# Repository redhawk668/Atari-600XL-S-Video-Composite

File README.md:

# Atari 600XL S-Video & Composite clean video.

I've designed this, because the 600XL doesn't have an s-video output. S-video output is actually a lot better than composite output. The composite output of the 600XL is quite bad, very blurry. After removing capacitor C109 it gets a lot less blurry, but it still isn't very nice to look at.

This circuit bypasses the 600XL's video circuit to get as clean as possible s-video output. It takes the signals straight from the GTIA, the luma signals are buffered with a 74HC4050 buffer/hex inverter, the buffer/resistor ladder is actually re-used from the original circuit. Chroma is passed through a resistor and a capacitor.
The resulting signals are then passed through a THS7314 filter/amplifier to create the seperate luma/chroma and composite signals.

It also provides composite output, not only s-video output. All signals are provided through the 5 pin DIN connector, they are compatible with existing s-video/composite cables.

It replaces the RF modulator, so that has to be removed. To expose the needed signals from the GTIA, pins 21,22,23,24,25 & 31 have to be lifted out of the socket and wires need to be soldered to those pins. Those will connect to the input pins on the s-video PCB. 

Although, this has been designed with the 600XL in mind, it should also work on the 800XL. The video circuit is basically the same as the 600XL's, only some older 800XL's don't have the chroma line connected. This PCB should solve that problem too.
However, the 800XLF has chroma connected. The XE series also have the chroma line connected. Unfortunatley. this PCB does not fit in the modulator space on an XE.

It provides improved video on NTSC machines as well.

# Rev. A

Top:

Bottom:

Installed in a 600XL:

# Billing of Materials:

|Qty |Value  |Component    |Package          |Parts                    |Description              |
|----|-------|-------------|-----------------|-------------------------|-------------------------|
| 7x | 1K    | Res805      | 0805            | R1,R2,R3,R4,R5,R14,R15  | Resistors               |
| 1x | 36K   | Res805      | 0805            | R6                      | Resistor                |
| 1x | 18K   | Res805      | 0805            | R7                      | Resistor                |
| 1x | 9K1   | Res805      | 0805            | R8                      | Resistor                |
| 1x | 4K7   | Res805      | 0805            | R9                      | Resistor                |
| 1x | 750R  | Res805      | 0805            | R10                     | Resistor                |
| 1x | 1K6   | Res805      | 0805            | R11                     | Resistor                |
| 1x | 2K    | Res805      | 0805            | R12                     | Resistor                |
| 1x | 18K   | Res805      | 0805            | R13                     | Resistor                |
| 3x | 75R   | Res805      | 0805            | R16,R17,R21             | Resistor                |
| 1x | 2K2   | Res805      | 0805            | R19                     | Resistor                |
| 2x | 3K3   | Res805      | 0805            | R20,R22                 | Resistor                |
| 1x | 22uF  | CP_Elec     | Can 6.3x5.3     | C1                      | Electrolytic Capacitor  |
| 5x | 0.1uF | Cap0805     | 0805            | C2,C3,C4,C5,C6          | Ceramic Capacitor       |
| 1x | 1N4148| DIODE323    | SOD-323         | CR1                     | 1N4148 Diode            |
| 1x | BC847 | Trans323    | SOT-323/SC70    | Q1                      | BC847 Transistor        |
| 1x | 4050  | HEXBuffer   | SOP-16          | U1                      | 74HC4050 Buffer         |
| 1x | 7314  | VideoFilter | SOIC-8          | U2                      | THS7314 Video/Filter    |
| 1x |       | Header      | 6x PinHeader    | GTIA Input              | 6x Angled PinHeader     |
| 1x |       | Header      | 3x PinHeader    | Output                  | 3x Straight PinHeader   |
| 1x |       | Header      | 2x PinHeader    | PCB mount               | 2x Straight PinHeader   |
| 1x |       | Header      | 3x PinHeader    | PCB Mount               | 3x Straight PinHeader   |

# Additional steps for installation in an NTSC 600XL

Installing the circuit in an NTSC 600XL is only marginally more difficult than the PAL version; three additional steps are required:

1. Desolder and remove the channel select switch
2. Install a 5-pin DIN PCB mount socket
3. Cut a suitable hole in the case for the DIN connector

Additional parts:

|Qty |Value  |Component    |Package          |Parts                    |Description              |
|----|-------|-------------|-----------------|-------------------------|-------------------------|
| 1x |       | Socket      | 5-pin DIN       | PCB Mount               | Standard DIN connector  |

You also need to make/purchase a 5-pin DIN composite/s-video/audio cable; the same one the Atari 800 uses (there are several good sources for pre-made cables)

# Detailed installation guide (PAL and NTSC 600XL)

This guide will point out differences between PAL and NTSC installation steps, where relevant.

Before you begin:

This project requires surface-mount soldering skills; most parts are fairly easy to work with - the diode and transistor are the smallest parts (SOD-323), with the diode pads being very small. Be sure you can solder SMD, or know someone who can.

The pre-generated Gerber files included in the repository should be directly 'uploadable' to most PCB manufacturers without modification. It is a 4-layer board - nothing out of the ordinary to note. The cost to manufacturer 5 boards is likely less than $20.

The parts list is accurate; most parts should be available and in stock from major electronic part suppliers.

Once you receive your PCB and parts, solder the parts to the board using your preferred method (solder, flux, wave, etc.) and check for any shorts or cold solder joints; the circuit is fairly small and should only take a few minutes to verify against the schematic. Your finished PCB should look similar to the following images. Note that the downward-facing PC pins are designed to fit into ground plane holes that used to hold the RF modulator.

Top View

Bottom View

Follow an online guide to open the 600XL, disconnect the keyboard, remove the main PCB and remove RF shielding, leaving just the main PCB. There are many excellent online guides available.

NTSC models: You'll need to desolder and remove the channel switch and identify the DIN jack placement.

Switch removal and DIN jack pads for NTSC

On the bottom of the PCB, the Chroma connector is tied to ground, which has to be broken for the modification to work. The trace on the PCB is fairly thick, but will still roll-up once you cut your way though with a sharp knife.

Bridge to Remove (PAL and NTSC)

For PAL and NTSC versions, the RF modulator needs to be removed. There are 8 points to desolder; the four wires are easy, the four RF case grounding pads are somewhat more stubborn.

RF Modulator Desolder Points

Once the modulator is removed, the next step is to solder the board into place. The ground pins on the board should fit into the RF case ground points (ensure as much solder as possible is removed from the holes to facilitate installation). The board should not make contact with the ground plane, but "float" a mm or two above the board surface. Position and solder the board, making sure it is square and not overhanging the back of the main PCB.

5-pin DIN Installation (NTSC)

Use a desoldering tool to remove residual solder from the DIN mounting holes, making sure the DIN socket dry-fits, including the front two stabilizing pins, which were previously hidden by the switch. Install and solder the DIN socket into place.

Installed Board and DIN socket

Lift GTIA Pins

6 pins on the GTIA chip need to be lifted outside the socket to disconnect them from the existing circuit and enable connection to the board. As mentioned above, the pins are: 21,22,23,24,25 & 31

GTIA Pins to be Lifted

Solder PC pin connectors, or straight wire onto the lifted pins to the corresponding pins on the board, being careful to avoid any shorts.

Power

Solder a PC pin connector or wire from the +5V pin to the third RF wire solder pad from the left.

Power Connector

Soldered to GTIA and Power

Connect output pins to DIN socket

The board generates Luma, Comp. and Chroma signals - all of which need to be connected to the DIN connector. For NTSC and PAL, the audio and ground pins are already connected on the board and no modification is necessary to these pins. 

5-pin DIN Connector

The Luma pad on PAL and NTSC boards is unpopulated - solder a PC pin connector or wire from the board Luma pin to the first DIN jack position. 

The Comp. pad on PAL is connected to a [formerly] active circuit - lift the leg of R137 closest to the DIN connector and solder the end of a PC pin connector or wire to the now vacant pad and connect to the Comp. output on the board. For NTSC, the R137 pad connected to pin 2 of the DIN connector should be unpopulated - solder the end of a PC pin connector to this pad and connect to the Comp. board output.

The DIN Chroma connector (pin 4) is unpopulated on PAL and NTSC boards, and should have been disconnected from ground by lifting the trace (as above). Solder a PC pin connector to the pad of DIN pin 4 and connect to the Chroma output of the board.

Output Connectors Soldered

If your PC pin connectors are tall, the output pins may need to be bent towards the DIN connector to allow the connectors to clear the RF shielding. Use pliers to bend the pins to a 45 degree angle and slightly towards the front of the PCB.

For NTSC boards, use a Dremel or equivalent tool to cut out a suitable hole for the DIN connector in the case. The hole is roughly centered horizontally on either side of the switch slot, and at the same height (and size) as the power DIN connector. You can use the power DIN connector as a template.

On PAL and NTSC boards, there will be a hole where the RF modulator used to be, which can be filled or capped. 

Follow an online guide to reassamble the 600XL and connect the DIN video connector to s-video and audio. Turn the power on and ensure your monitor is set to s-video. You should see a picture, but the tint will likely be off. Use the tint adjustment on your monitor to adjust the tint until it looks correct. At the same time, adjust brightness and contrast to appropriate levels. The picture should be very clear with practically no interference. If your monitor does not have s-video, the board also outputs composite video, which is very clear as well. Connect composite and audio connectors from the DIN cable to your monitor and adjust. Examples of s-video picture quality from an LCD monitor below.

Close up of READY

Track and Field Title

Track and Field

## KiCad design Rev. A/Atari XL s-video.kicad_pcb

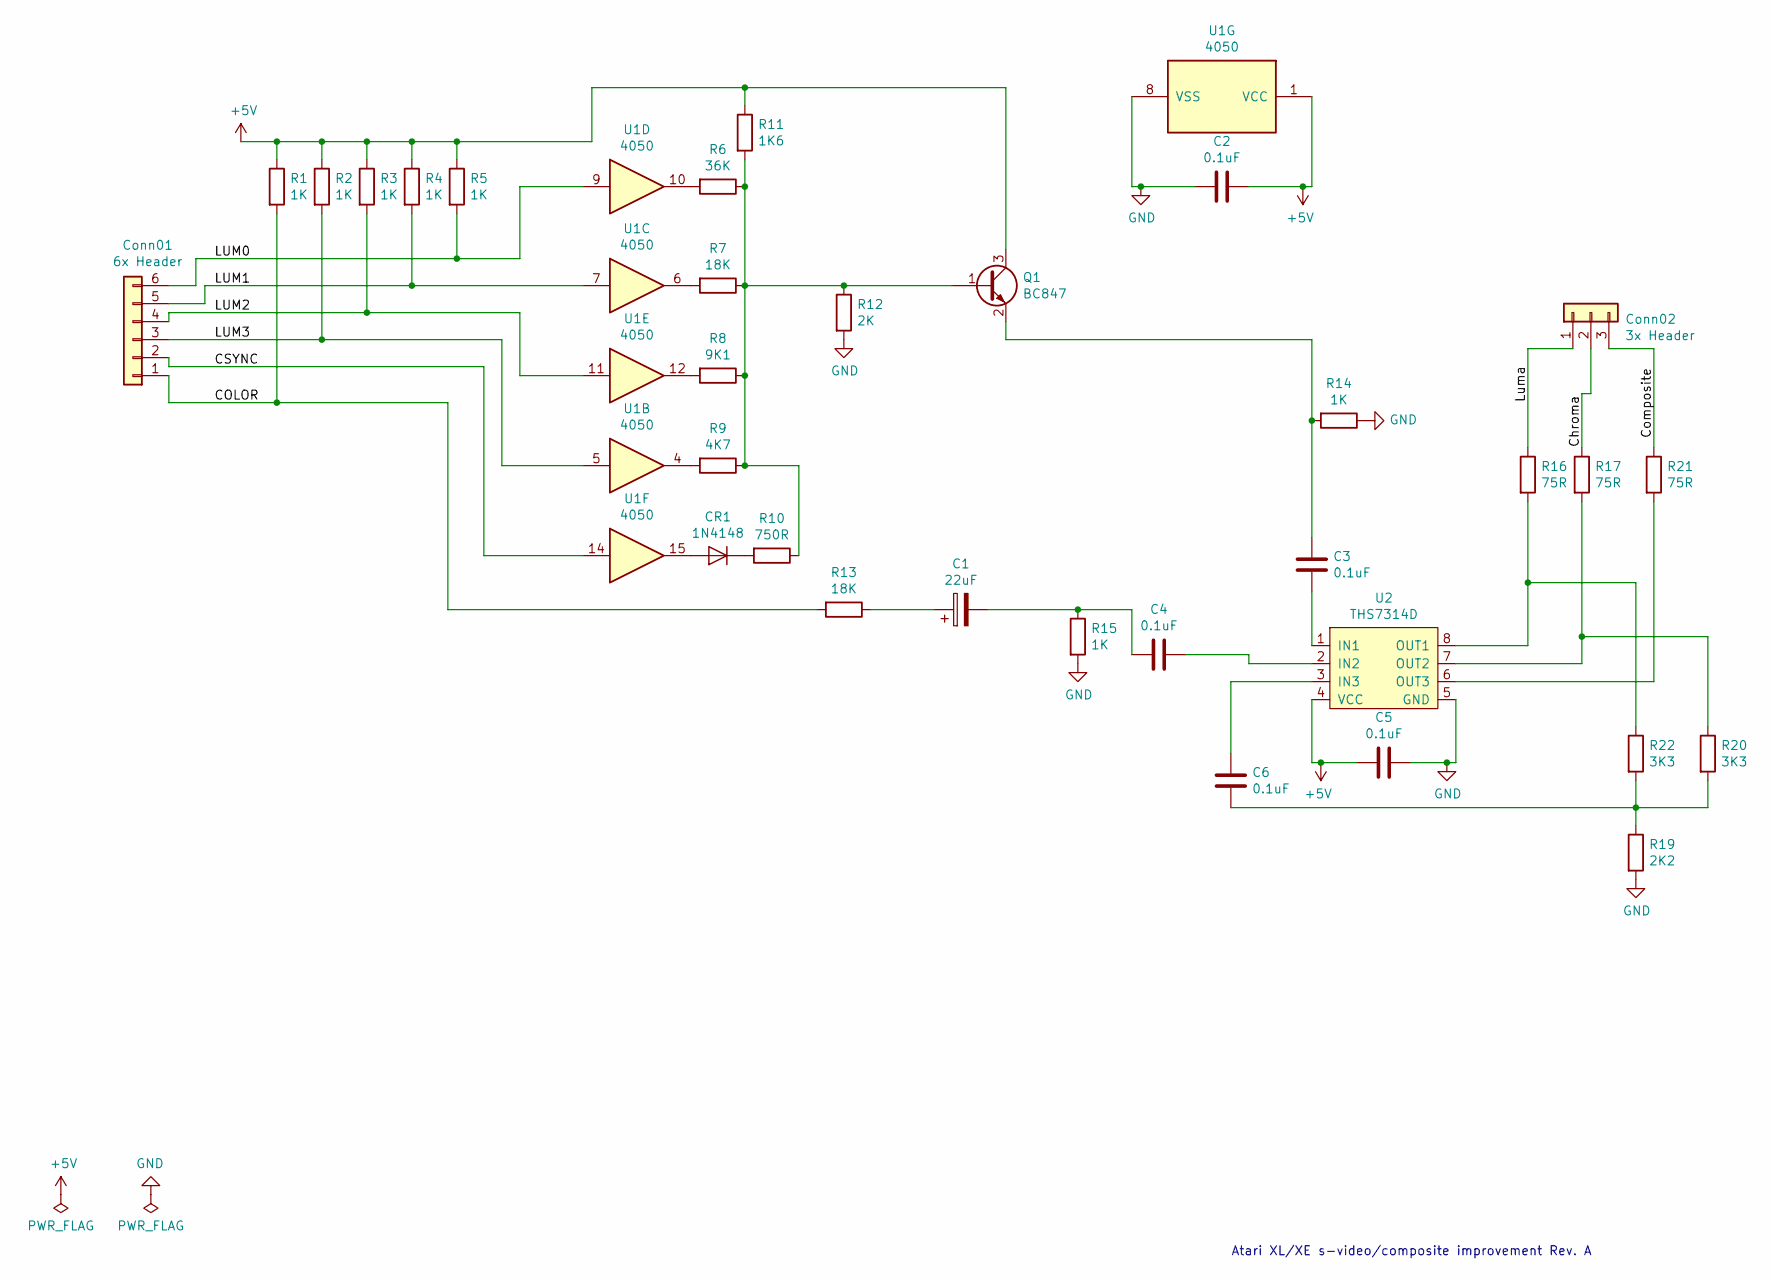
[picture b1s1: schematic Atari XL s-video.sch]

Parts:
C1: 22uF; CP_Elec_6.3x5.3
C2, C3, C4, C5, C6: 0.1uF; C_0805_HandSoldering
CR1: 1N4148; D_SOD-323
Conn01: 6x Header; PINHEAD1-6
Conn02: 3x Header; PINHEAD1-3
Q1: BC847; SOT-323_SC-70_Handsoldering
R1, R2, R3, R4, R5, R14, R15: 1K; R_0805_HandSoldering
R6: 36K; R_0805_HandSoldering
R7, R13: 18K; R_0805_HandSoldering
R8: 9K1; R_0805_HandSoldering
R9: 4K7; R_0805_HandSoldering
R10: 750R; R_0805_HandSoldering
R11: 1K6; R_0805_HandSoldering
R12: 2K; R_0805_HandSoldering
R16, R17, R21: 75R; R_0805_HandSoldering
R19: 2K2; R_0805_HandSoldering
R20, R22: 3K3; R_0805_HandSoldering
U1: 4050; SO-16-N
U2: THS7314D; SOIC-8-N

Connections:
+5V: C2.1, C5.2, Q1.3 (C), R1.1, R2.1, R3.1, R4.1, R5.1, R11.1, U1.1 (VCC), U2.4 (VCC); also elsewhere on the board
/COLOR: Conn01.1, R1.2, R13.2; also elsewhere on the board
/CSYNC: Conn01.2, U1.14; also elsewhere on the board
/Chroma: Conn02.2, R17.1; also elsewhere on the board
/Composite: Conn02.3, R21.1; also elsewhere on the board
/LUM0: Conn01.6, R5.2, U1.9; also elsewhere on the board
/LUM1: Conn01.5, R4.2, U1.7; also elsewhere on the board
/LUM2: Conn01.4, R3.2, U1.11; also elsewhere on the board
/LUM3: Conn01.3, R2.2, U1.5; also elsewhere on the board
/Luma: Conn02.1, R16.1; also elsewhere on the board
GND: C2.2, C5.1, R12.2, R14.1, R15.2, R19.2, U1.8 (VSS), U2.5 (GND); also elsewhere on the board
unnamed: C1.1, R13.1
unnamed: C1.2, C4.2, R15.1
unnamed: C3.1, Q1.2 (E), R14.2
unnamed: C3.2, U2.1 (IN1)
unnamed: C4.1, U2.2 (IN2)
unnamed: C6.1, U2.3 (IN3)
unnamed: C6.2, R19.1, R20.2, R22.2
unnamed: CR1.1 (K), R10.2
unnamed: CR1.2 (A), U1.15
unnamed: Q1.1 (B), R6.1, R7.1, R8.1, R9.1, R10.1, R11.2, R12.1
unnamed: R6.2, U1.10
unnamed: R7.2, U1.6
unnamed: R8.2, U1.12
unnamed: R9.2, U1.4
unnamed: R16.2, R22.1, U2.8 (OUT1)
unnamed: R17.2, R20.1, U2.7 (OUT2)
unnamed: R21.2, U2.6 (OUT3)

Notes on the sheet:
Atari XL/XE s-video/composite improvement Rev. A

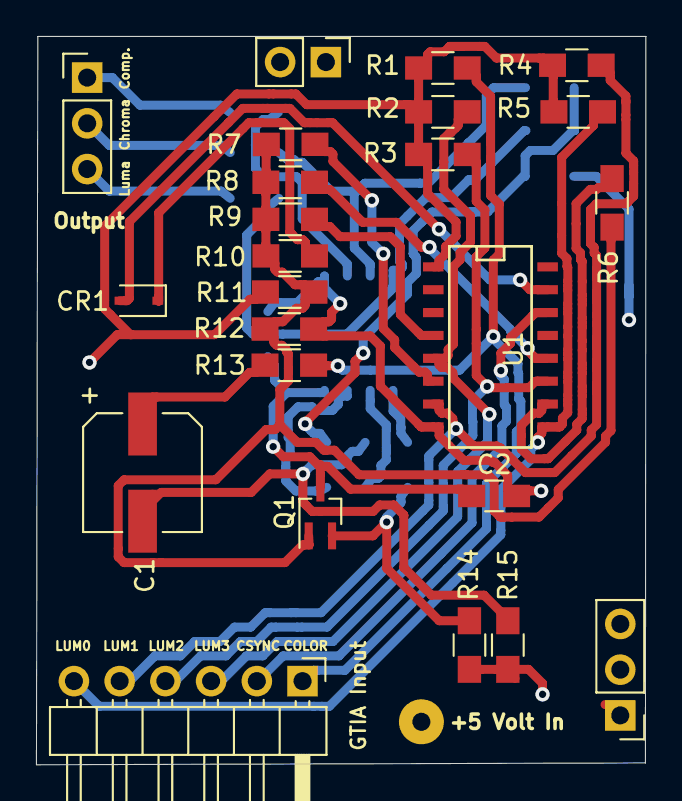
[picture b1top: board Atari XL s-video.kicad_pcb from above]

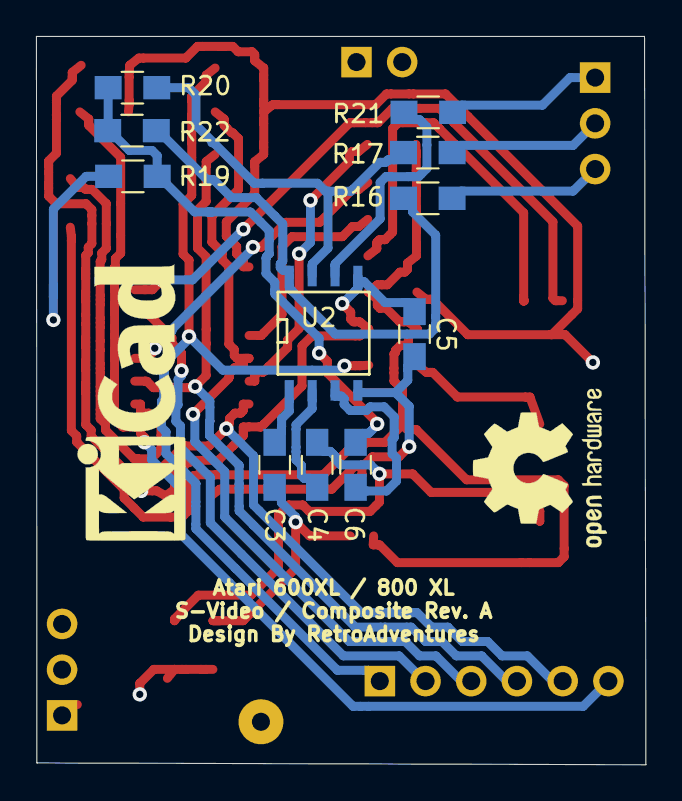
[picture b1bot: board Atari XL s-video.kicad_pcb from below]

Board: 4 copper layers, 33.9 x 40.5 mm, 38 parts (13 on the bottom side), 28 nets.

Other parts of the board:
5 Volt Input: SolderWirePad_single_1mmDrill
GTIA Input: 6x Header; Pin_Header_Angled_1x06_Pitch2.54mm
Logo: KiCad-Logo_6mm_SilkScreen
Mount2: Pin_Header_Straight_1x03_Pitch2.54mm
Mount3: Pin_Header_Straight_1x02_Pitch2.54mm
OSHW Logo: OSHW-Logo2_9.8x8mm_SilkScreen
Output: Pin_Header_Straight_1x03_Pitch2.54mm

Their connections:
+5V: 5 Volt Input.1; also elsewhere on the board
/COLOR: GTIA Input.1; also elsewhere on the board
/CSYNC: GTIA Input.2; also elsewhere on the board
/Chroma: Output.2; also elsewhere on the board
/Composite: Output.1; also elsewhere on the board
/LUM0: GTIA Input.6; also elsewhere on the board
/LUM1: GTIA Input.5; also elsewhere on the board
/LUM2: GTIA Input.4; also elsewhere on the board
/LUM3: GTIA Input.3; also elsewhere on the board
/Luma: Output.3; also elsewhere on the board
GND: Mount2.1, Mount2.2, Mount2.3, Mount3.1, Mount3.2; also elsewhere on the board

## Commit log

2021-01-18 Create LICENSE
2022-03-21 Update Readme.md
    This is an excellent board and modification - the output is incredibly clear, but the installation instructions were a bit 'brief' and PAL-specific. This readme update expands the installation instru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
2022-03-22 Corrected "SOT" to "SOD"
